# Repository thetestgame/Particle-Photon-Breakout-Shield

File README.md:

# Particle Photon Breakout Shield
<b>Revision. B</b><br/>
A Shield for the Particle Photon/Core for breaking out the pinouts to terminal blocks for easy prototype wiring without a breadboard.
<br/><br/>
<a href="https://oshpark.com/shared_projects/EYhMceqL"></img></a><br/>

### License
<a href="https://github.com/thetestgame/Particle-Photon-Breakout-Shield/blob/master/LICENSE">MIT</a>

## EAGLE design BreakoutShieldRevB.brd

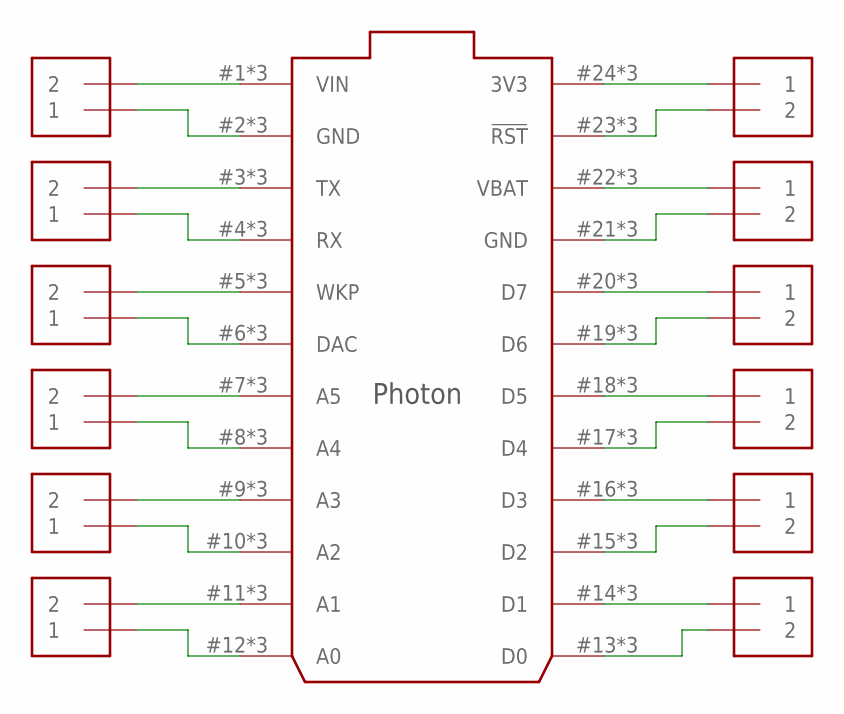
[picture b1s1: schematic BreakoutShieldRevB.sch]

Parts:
J1, J2, J3, J4, J5, J6, J7, J8, J9, J10, J11, J12: 1X2-3.5MM
U$1: PHOTON_WITH_STACKABLE_HEADERS; PHOTON_STACKABLE

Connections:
unnamed: J1.2, U$1.1 (VIN), U$1.#1 (VIN), U$1.@1 (VIN)
unnamed: J1.1, U$1.2 (GND), U$1.#2 (GND), U$1.@2 (GND)
unnamed: J2.2, U$1.3 (TX), U$1.#3 (TX), U$1.@3 (TX)
unnamed: J2.1, U$1.4 (RX), U$1.#4 (RX), U$1.@4 (RX)
unnamed: J3.2, U$1.5 (WKP), U$1.#5 (WKP), U$1.@5 (WKP)
unnamed: J3.1, U$1.6 (DAC), U$1.#6 (DAC), U$1.@6 (DAC)
unnamed: J4.2, U$1.7 (A5), U$1.#7 (A5), U$1.@7 (A5)
unnamed: J4.1, U$1.8 (A4), U$1.#8 (A4), U$1.@8 (A4)
unnamed: J5.2, U$1.9 (A3), U$1.#9 (A3), U$1.@9 (A3)
unnamed: J5.1, U$1.10 (A2), U$1.#10 (A2), U$1.@10 (A2)
unnamed: J6.2, U$1.11 (A1), U$1.#11 (A1), U$1.@11 (A1)
unnamed: J6.1, U$1.12 (A0), U$1.#12 (A0), U$1.@12 (A0)
unnamed: J7.1, U$1.24 (3V3), U$1.#24 (3V3), U$1.@24 (3V3)
unnamed: J7.2, U$1.23 (!RST), U$1.#23 (!RST), U$1.@23 (!RST)
unnamed: J8.1, U$1.22 (VBAT), U$1.#22 (VBAT), U$1.@22 (VBAT)
unnamed: J8.2, U$1.21 (GND), U$1.#21 (GND), U$1.@21 (GND)
unnamed: J9.1, U$1.20 (D7), U$1.#20 (D7), U$1.@20 (D7)
unnamed: J9.2, U$1.19 (D6), U$1.#19 (D6), U$1.@19 (D6)
unnamed: J10.1, U$1.18 (D5), U$1.#18 (D5), U$1.@18 (D5)
unnamed: J10.2, U$1.17 (D4), U$1.#17 (D4), U$1.@17 (D4)
unnamed: J11.1, U$1.16 (D3), U$1.#16 (D3), U$1.@16 (D3)
unnamed: J11.2, U$1.15 (D2), U$1.#15 (D2), U$1.@15 (D2)
unnamed: J12.1, U$1.14 (D1), U$1.#14 (D1), U$1.@14 (D1)
unnamed: J12.2, U$1.13 (D0), U$1.#13 (D0), U$1.@13 (D0)

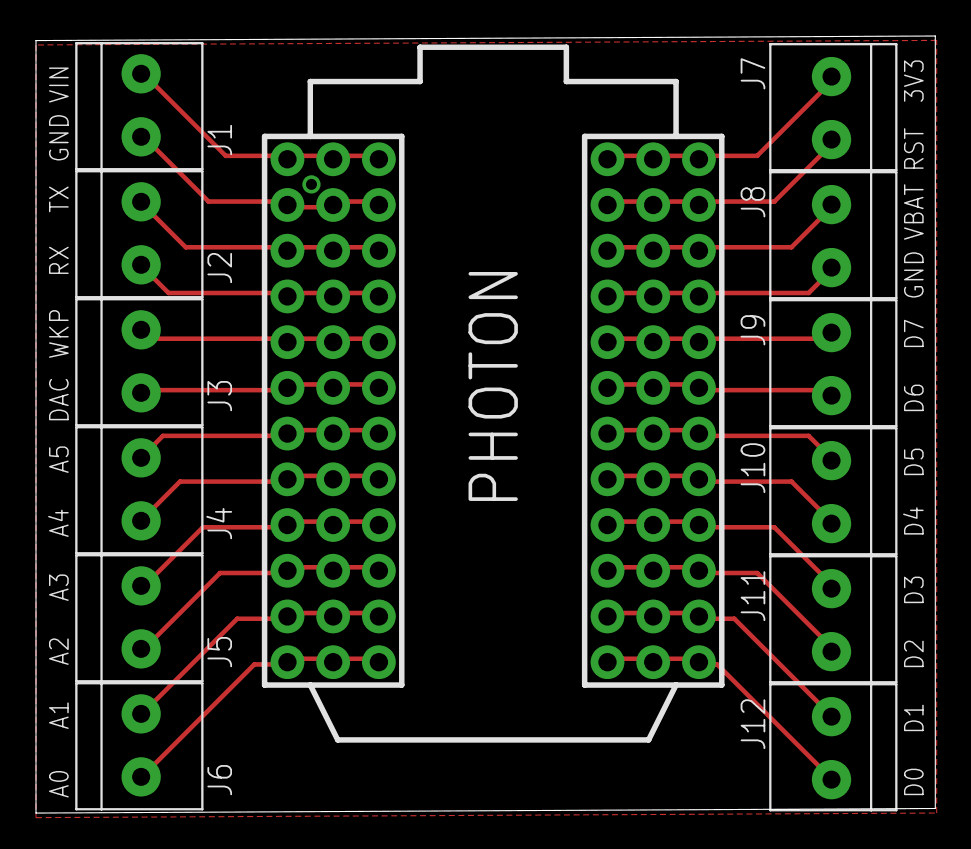
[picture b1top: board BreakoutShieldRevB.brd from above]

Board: 2 copper layers, 50.0 x 43.2 mm, 13 parts (0 on the bottom side), 24 nets.

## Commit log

2016-03-23 Added Revision B
